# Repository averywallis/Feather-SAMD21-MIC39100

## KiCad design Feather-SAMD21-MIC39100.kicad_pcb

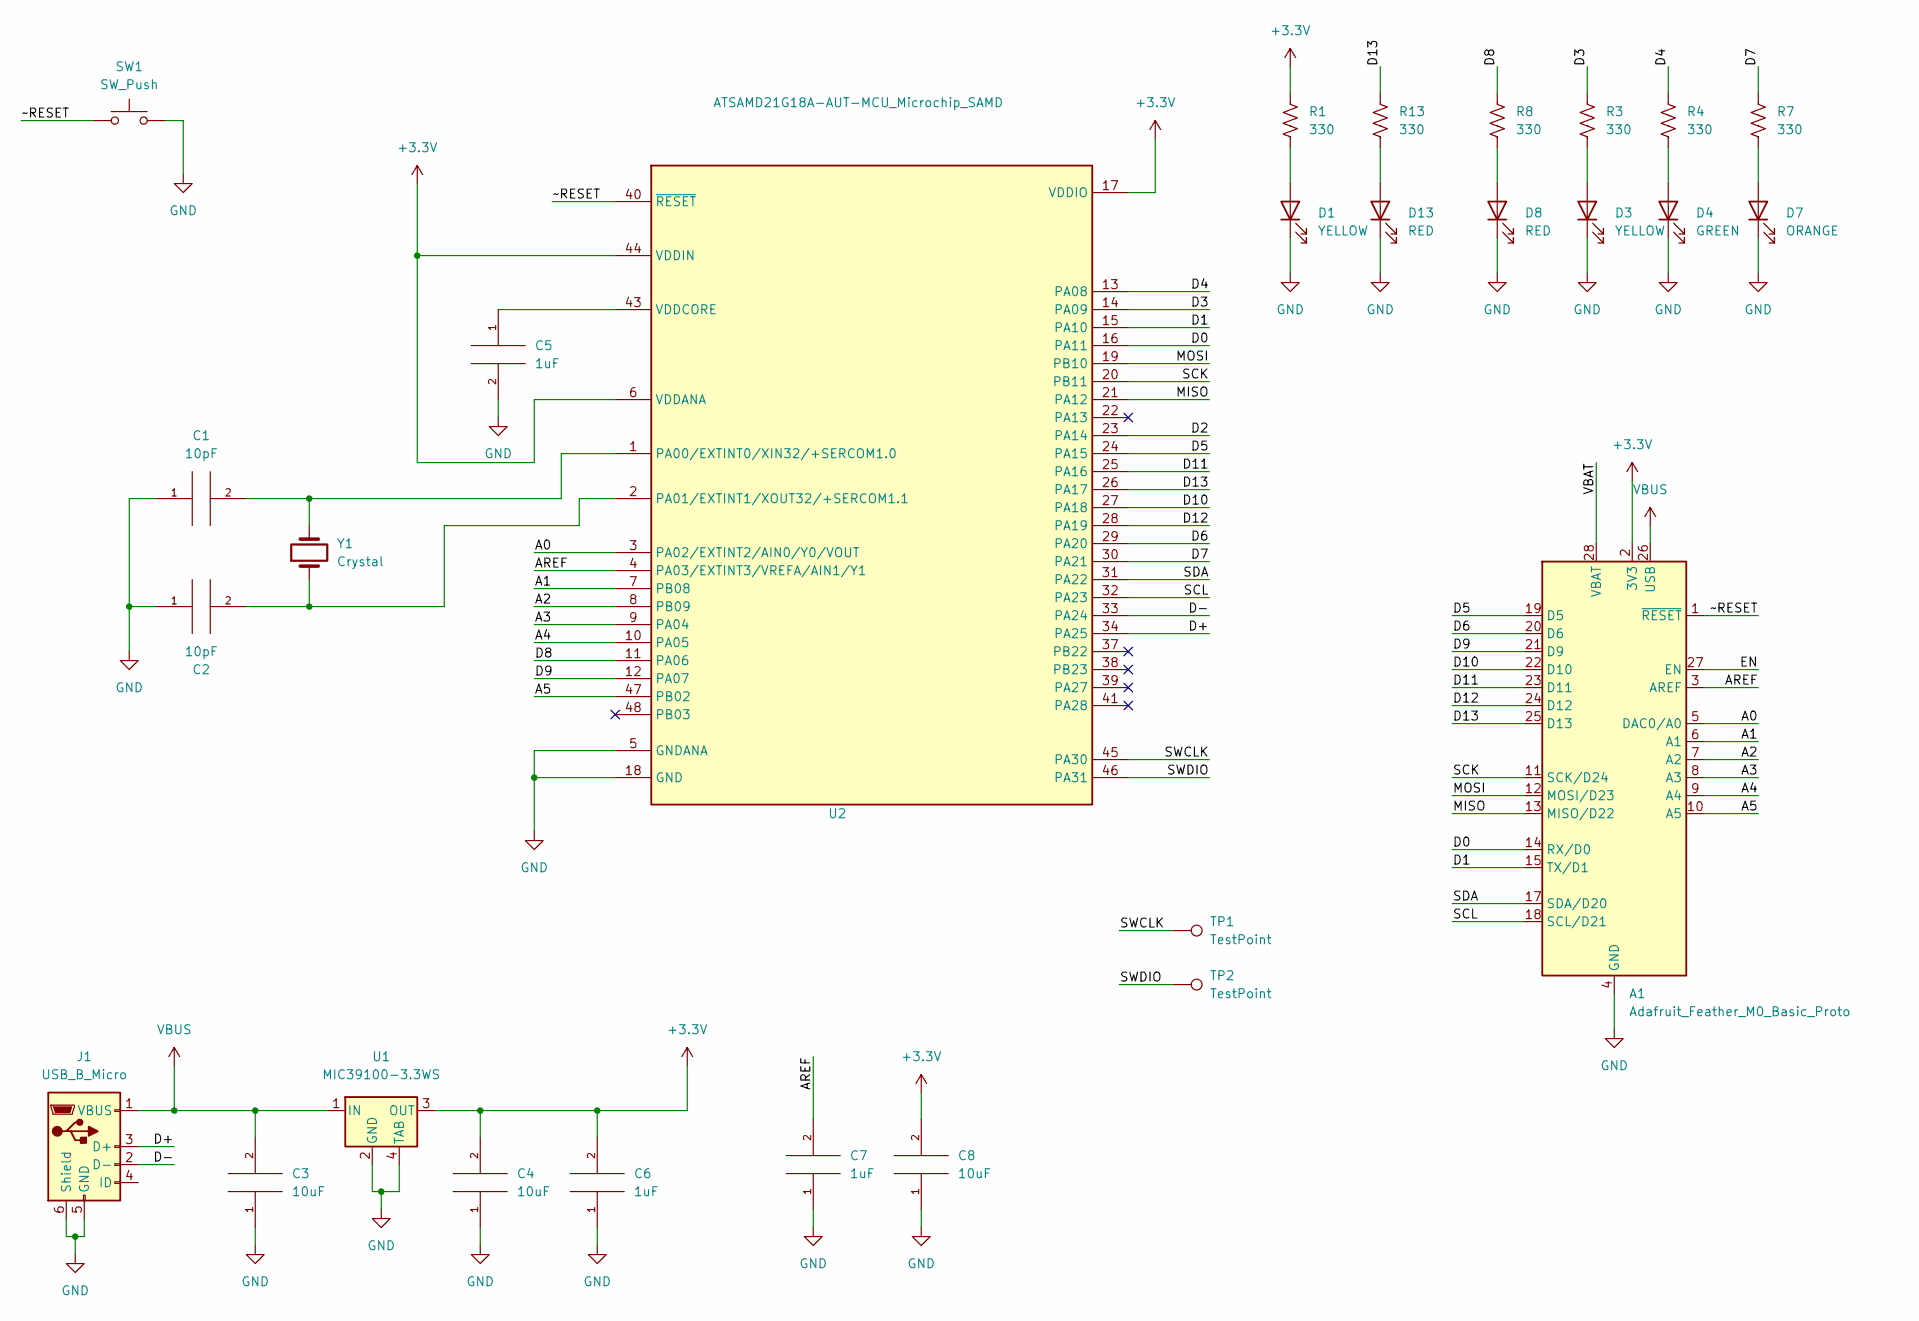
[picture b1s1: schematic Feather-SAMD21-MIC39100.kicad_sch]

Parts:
A1: Adafruit_Feather_M0_Basic_Proto; Adafruit_Feather_WithMountingHoles
C1, C2: 10pF; C_0603_1608Metric_Pad1.08x0.95mm_HandSolder
C3, C4, C8: 10uF; C_0603_1608Metric_Pad1.08x0.95mm_HandSolder
C5, C6, C7: 1uF; C_0603_1608Metric_Pad1.08x0.95mm_HandSolder
D1, D3: YELLOW; LED_0603_1608Metric_Pad1.05x0.95mm_HandSolder
D4: GREEN; LED_0603_1608Metric_Pad1.05x0.95mm_HandSolder
D7: ORANGE; LED_0603_1608Metric_Pad1.05x0.95mm_HandSolder
D8, D13: RED; LED_0603_1608Metric_Pad1.05x0.95mm_HandSolder
J1: USB_B_Micro; USB_Micro-B_Molex-105017-0001
R1, R3, R4, R7, R8, R13: 330; R_0603_1608Metric_Pad0.98x0.95mm_HandSolder
SW1: SW_Push; SW_Push_1P1T_NO_CK_KMR2
TP1, TP2: TestPoint; TestPoint_Pad_D1.0mm
U1: MIC39100-3.3WS; SOT-223
U2: ATSAMD21G18A-AUT-MCU_Microchip_SAMD; TQFP-48_7x7mm_P0.5mm
Y1: Crystal; Crystal_SMD_3215-2Pin_3.2x1.5mm

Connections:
+3V3: A1.2 (3V3), C4.2, C6.2, C8.2, R1.1, U1.3 (OUT), U2.6 (VDDANA), U2.17 (VDDIO), U2.36 (VDDIO), U2.44 (VDDIN)
/A0: A1.5 (DAC0/A0), U2.3 (PA02/EXTINT2/AIN0/Y0/VOUT)
/A1: A1.6 (A1), U2.7 (PB08)
/A2: A1.7 (A2), U2.8 (PB09)
/A3: A1.8 (A3), U2.9 (PA04)
/A4: A1.9 (A4), U2.10 (PA05)
/A5: A1.10 (A5), U2.47 (PB02)
/AREF: A1.3 (AREF), C7.2, U2.4 (PA03/EXTINT3/VREFA/AIN1/Y1)
/D0: A1.14 (RX/D0), U2.16 (PA11)
/D1: A1.15 (TX/D1), U2.15 (PA10)
/D2: U2.23 (PA14)
/D3: R3.1, U2.14 (PA09)
/D4: R4.1, U2.13 (PA08)
/D5: A1.19 (D5), U2.24 (PA15)
/D6: A1.20 (D6), U2.29 (PA20)
/D7: R7.1, U2.30 (PA21)
/D8: R8.1, U2.11 (PA06)
/D9: A1.21 (D9), U2.12 (PA07)
/D10: A1.22 (D10), U2.27 (PA18)
/D11: A1.23 (D11), U2.25 (PA16)
/D12: A1.24 (D12), U2.28 (PA19)
/D13: A1.25 (D13), R13.1, U2.26 (PA17)
/D+: J1.3 (D+), U2.34 (PA25)
/D-: J1.2 (D-), U2.33 (PA24)
/EN: A1.27 (EN)
/MISO: A1.13 (MISO/D22), U2.21 (PA12)
/MOSI: A1.12 (MOSI/D23), U2.19 (PB10)
/SCK: A1.11 (SCK/D24), U2.20 (PB11)
/SCL: A1.18 (SCL/D21), U2.32 (PA23)
/SDA: A1.17 (SDA/D20), U2.31 (PA22)
/SWCLK: TP1.1, U2.45 (PA30); also elsewhere on the board
/SWDIO: TP2.1, U2.46 (PA31); also elsewhere on the board
/VBAT: A1.28 (VBAT)
/~RESET: A1.1 (~RESET), SW1.1, U2.40 (~RESET)
GND: A1.4 (GND), A1.16 (GND), C1.1, C2.1, C3.1, C4.1, C5.2, C6.1, C7.1, C8.1, D1.1 (K), D3.1 (K), D4.1 (K), D7.1 (K), D8.1 (K), D13.1 (K), J1.5 (GND), J1.6 (Shield), SW1.2, U1.2 (GND), U1.4 (TAB), U2.5 (GNDANA), U2.18 (GND), U2.35 (GND), U2.42 (GND)
unnamed: C1.2, U2.1 (PA00/EXTINT0/XIN32/+SERCOM1.0), Y1.2
unnamed: C2.2, U2.2 (PA01/EXTINT1/XOUT32/+SERCOM1.1), Y1.1
unnamed: C5.1, U2.43 (VDDCORE)
unnamed: D1.2 (A), R1.2
unnamed: D3.2 (A), R3.2
unnamed: D4.2 (A), R4.2
unnamed: D7.2 (A), R7.2
unnamed: D8.2 (A), R8.2
unnamed: D13.2 (A), R13.2
VBUS: A1.26 (USB), C3.2, J1.1 (VBUS), U1.1 (IN)

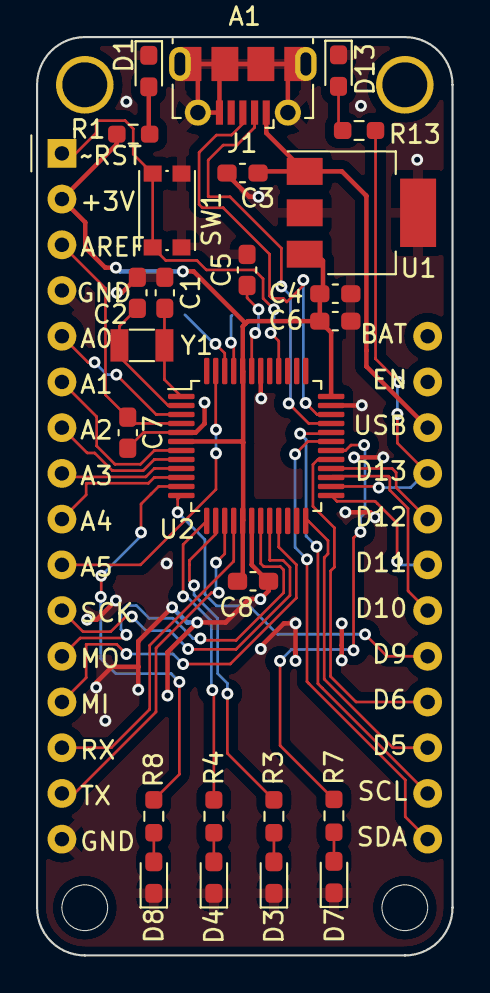
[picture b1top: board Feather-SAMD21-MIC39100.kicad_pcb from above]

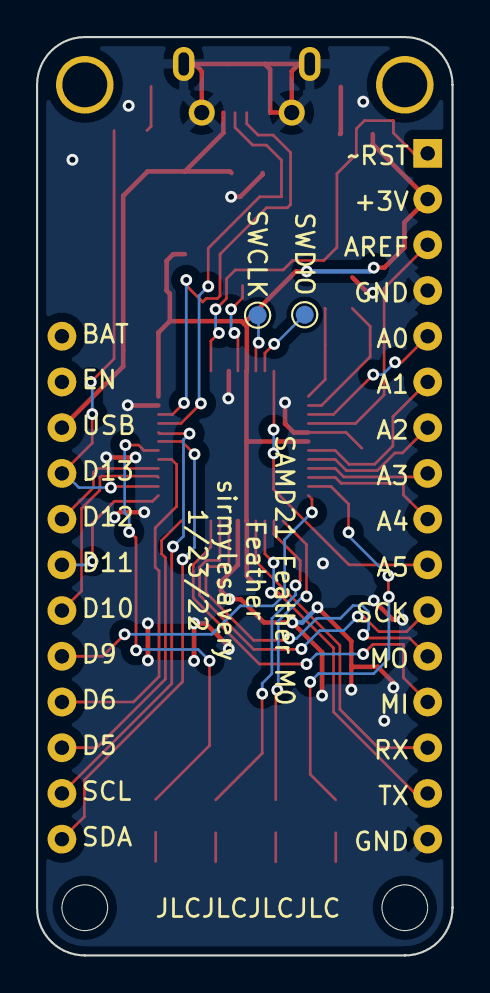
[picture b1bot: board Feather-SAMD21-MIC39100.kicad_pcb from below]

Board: 2 copper layers, 23.1 x 51.0 mm, 28 parts (2 on the bottom side), 42 nets.

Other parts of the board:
SWCLK: TestPoint; TestPoint_Pad_D1.0mm
SWDIO: TestPoint; TestPoint_Pad_D1.0mm

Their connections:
/SWCLK: SWCLK.1; also elsewhere on the board
/SWDIO: SWDIO.1; also elsewhere on the board

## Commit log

2022-01-29 Create LICENSE
